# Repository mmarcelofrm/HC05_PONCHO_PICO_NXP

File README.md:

HC05_PONCHO_PICO_NXP

Autor: Marcelo Franz Moreno Marin

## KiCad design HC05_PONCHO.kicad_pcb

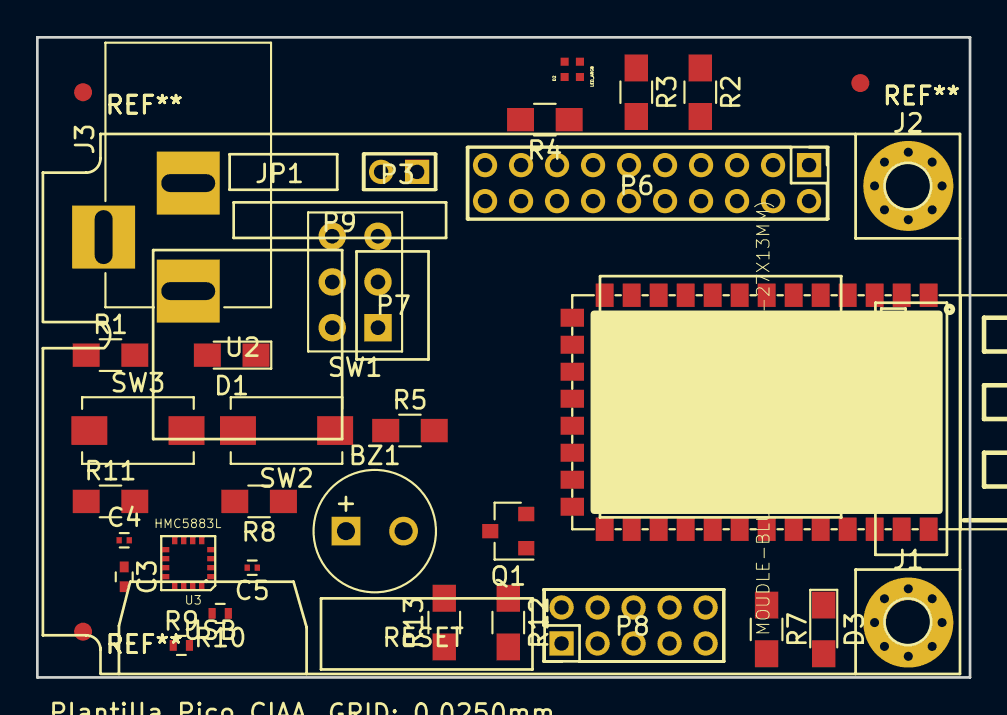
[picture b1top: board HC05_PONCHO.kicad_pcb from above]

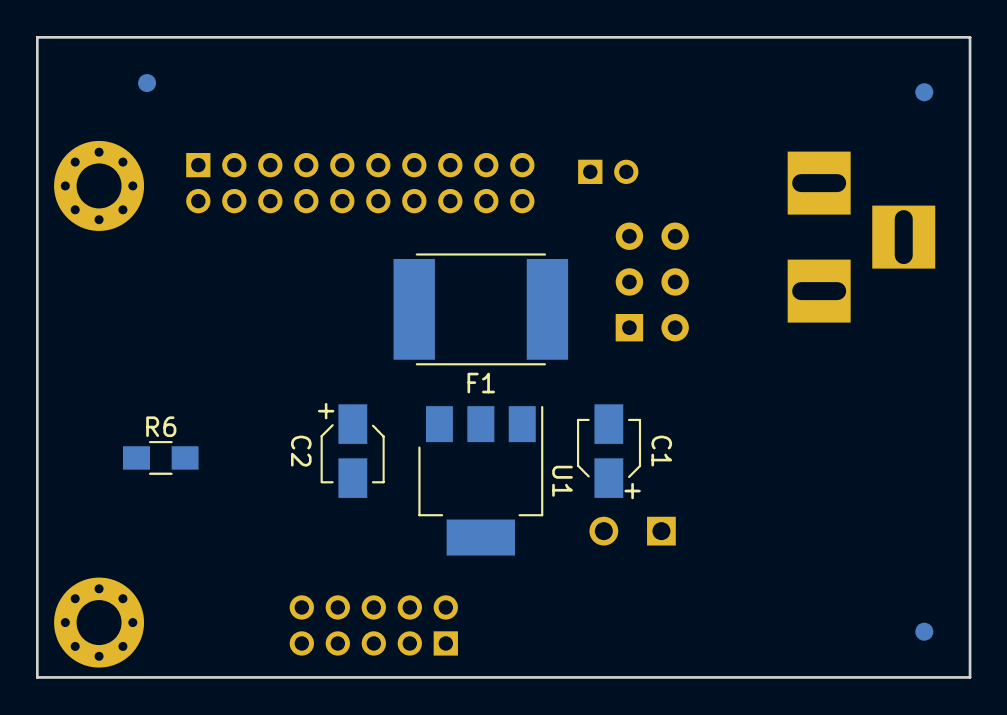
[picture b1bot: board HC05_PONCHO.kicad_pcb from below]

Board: 2 copper layers, 51.8 x 35.6 mm, 35 parts (5 on the bottom side), 32 nets, no tracks yet.

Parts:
BZ1: Buzzer; MagneticBuzzer_Kingstate_KCG0601
C1: 10uF/16V; CP_Elec_3x5.3
C2: 100nF/25V; CP_Elec_3x5.3
C3: 4.7uF; C_0402
C4: 0.22uF; C_0201
C5: 0.1uF; C_0201
Conn1: Conn_Pico; Conn_Pico_Ciaa
D1: LED/RED; LED_0805_HandSoldering
D2: LED_ARGB; DIOC0404X01-4N
D3: LED/BLUE; LED_0805_HandSoldering
F1: Fuse; Fuse_SMD2920
J1, J2: MOUNT_HOLE; MountingHole_2.5mm_Pad_Via
J3: BARREL_JACK
Plantilla_Pico_CIAA: Plantilla_Pico
Q1: Q_NPN_EBC; SOT-23
R1, R2, R3, R4, R5, R6, R7, R13: 470; R_0805_HandSoldering
R8, R11, R12: 10K; R_0805_HandSoldering
R9, R10: 2K2; R_0402
SW1: SW_SPDT; SW_NKK_G1xJP
SW2, SW3: SW_Push; SW_SPST_EVQPE1
U1: LD1117S33CTR; SOT-223
U2: MOUDLE-BLUETOOTH-HC-05(34P-27X13MM); BT34P-SMD-1.5-26.9X13.0X2.2MM
U3: HMC5883L; LPCC-16

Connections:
+3V3: BZ1.1, C1.1, C5.2, Conn1.15, D2.1, R1.1, R9.1, R10.1, R13.1, SW2.2, SW3.2, U1.2, U2.12, U3.2, U3.4, U3.13
GND: C1.2, C2.2, C3.2, C5.1, Conn1.16, Conn1.45, D1.1, D3.1, J1.1, J2.1, J3.2, Q1.1, R8.2, R11.2, U1.1, U2.13, U2.22, U3.9, U3.11
HC05-RST: Conn1.43, U2.11
unnamed: BZ1.2, Q1.3
unnamed: C2.1, F1.2, U1.3
unnamed: C3.1, U3.10
unnamed: C4.1, U3.12
unnamed: C4.2, U3.8
unnamed: Conn1.17, U2.3
unnamed: Conn1.18, U2.4
unnamed: Conn1.20, U2.5
unnamed: Conn1.25, R2.2
unnamed: Conn1.29, R3.2
unnamed: Conn1.33, R4.2
unnamed: Conn1.37, R11.1, SW3.1, U2.2
unnamed: Conn1.38, R5.2
unnamed: Conn1.39, R10.2, U3.1
unnamed: Conn1.40, R13.2, U2.1
unnamed: Conn1.41, R12.2
unnamed: Conn1.42, R9.2, U3.16
unnamed: Conn1.44, R6.2
unnamed: D1.2, R1.2
unnamed: D2.2, R2.1
unnamed: D2.3, R3.1
unnamed: D2.4, R4.1
unnamed: D3.2, R7.2
unnamed: F1.1, SW1.2
unnamed: J3.1, SW1.1
unnamed: Q1.2, R12.1
unnamed: R5.1, R8.1, SW2.1, U2.34
unnamed: R6.1, U2.32
unnamed: R7.1, U2.31

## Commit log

2017-04-19 Creacion de repositorio HC05_Poncho. Modulo Bluetooth para PICO CIAA
2017-04-19 Actualizacion de info
    Creacion y reorganizacion por carpetas.
    Adicion de datasheets para el proyecto(Buzzers, regulador lineas, modulo bluetooth, giroscopio y picoCIAA).
    Actualizacion de Readme.
    Adicion de esquematico para la fuente.
2017-04-24 Inicio de schematico
    - Creacion de regulador de tension.
    - Cracion de modulo acelerometro.
2017-05-17 Actualizacion de esquematico
    -Esquematico graficamente completo.
    -Reorganizacion por interfaces.
    -Se completan los requerimientos.
    Falta:
    -revision externa.
    -numeracion de componentes.
2017-05-17 Finalizacion de esquematico
    - Componentes numerados.
    falta revision externa
2017-06-05 Asociacion footprints - inicio de PCB
    Asociacion de footprints correspondientes para inicio de PCB
2017-06-11 Primera revisión del esquemático
    > Se agrega y completa el documento de revisión realizada al momento del tag schematicToReview.
2017-06-18 Esquematico V1.1
    Correccion parcial de las observaciones realizadas por el revisor, se reflejan el archivo de revision ubicado en la carpeta doc
2017-07-28 Avance para segunda revision.
    Se realizan todos los cambios solicitados por el docente y el corrector, ademas se continua con el avance hasta el placement del PCB
2017-07-28 Revision de carpetas
    Limpieza de documentos que ya no se utilizaban en el proyecto.

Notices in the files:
HC05_PONCHO.kicad_pcb:
GNU GPL License
